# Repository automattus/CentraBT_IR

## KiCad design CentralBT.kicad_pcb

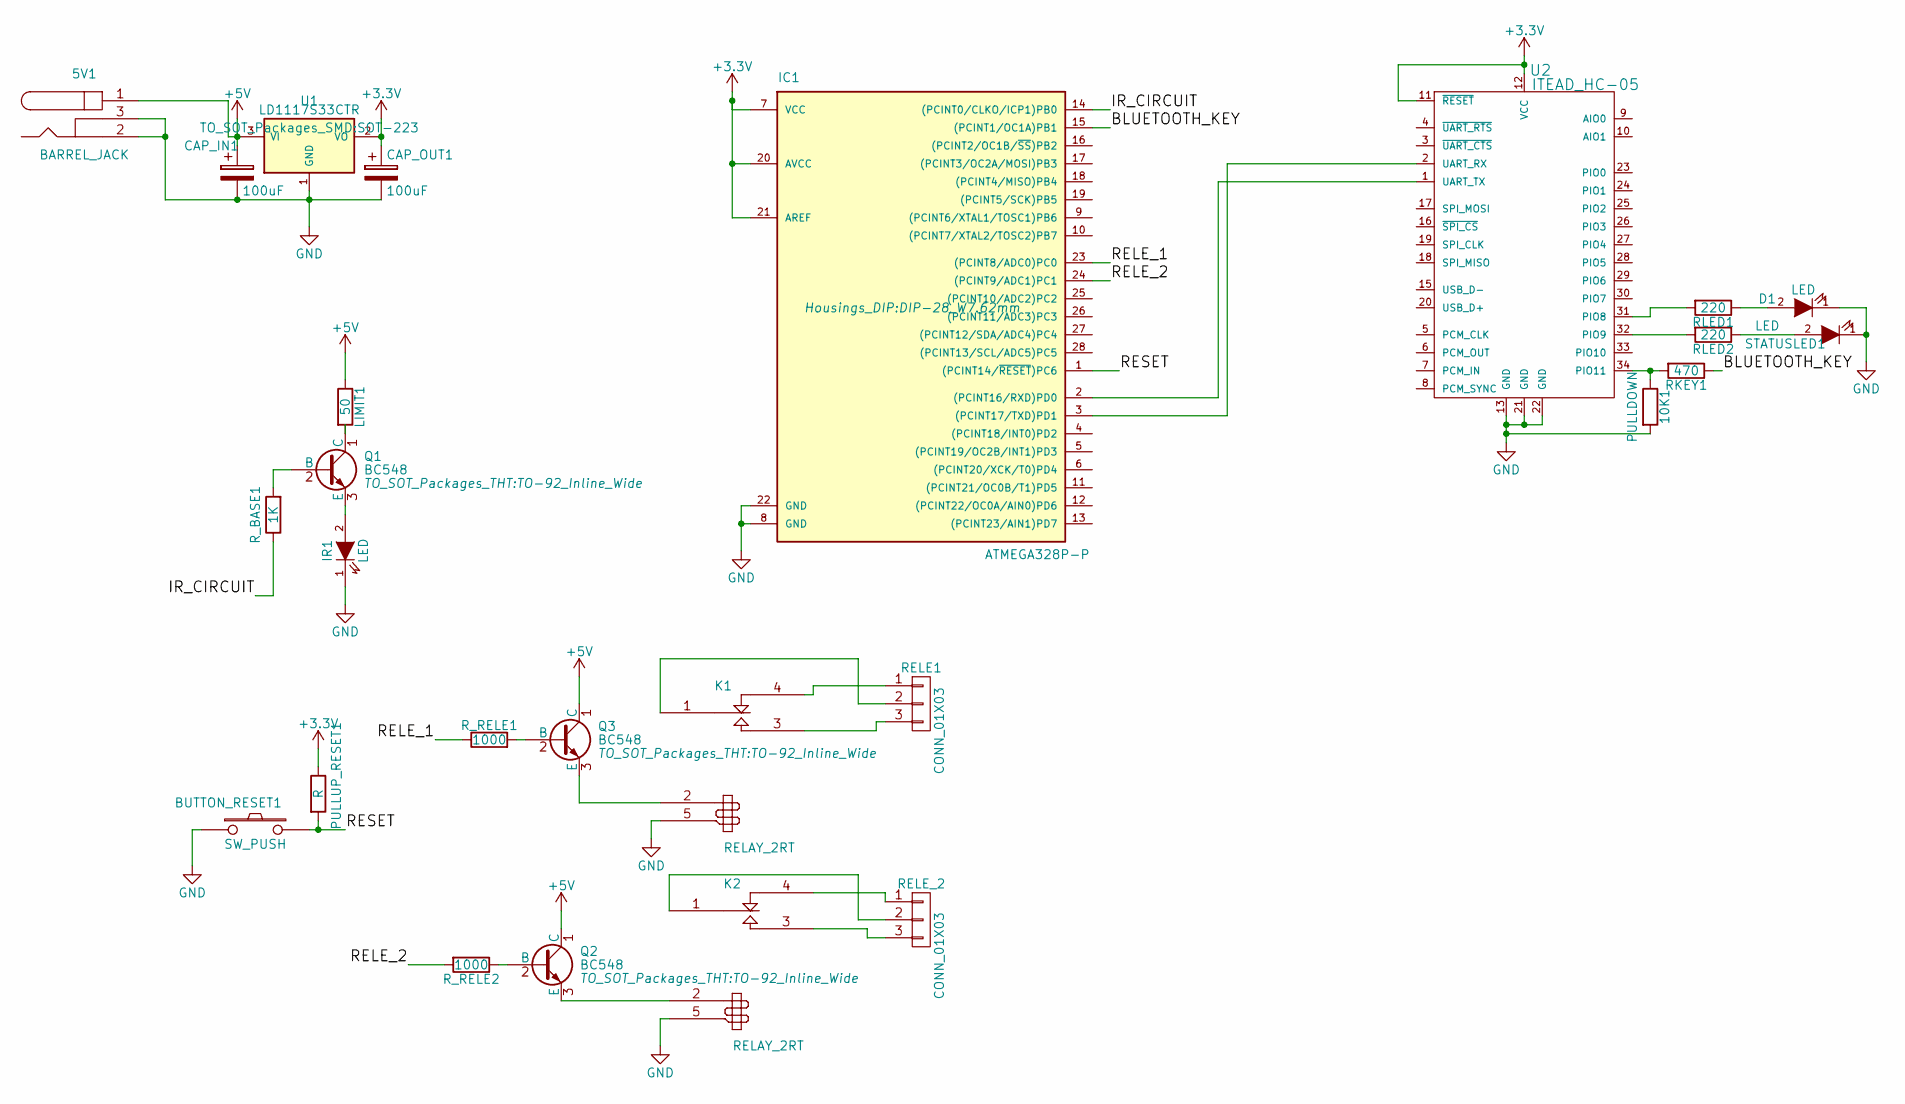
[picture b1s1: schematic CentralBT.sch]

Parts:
5V1: BARREL_JACK
10K1: PULLDOWN; Resistor_Horizontal_RM7mm
BUTTON_RESET1: SW_PUSH; SW_PUSH_SMALL
CAP_IN1: 100uF; C_Radial_D5_L6_P2.5
CAP_OUT1: 100uF; C_Radial_D5_L6_P2.5
D1: LED; LED-3MM
IC1: ATMEGA328P-P; DIP-28_W7.62mm
IR1: LED; LED-5MM
K1, K2: RELAY_2RT; Relay_SANYOU_SRD_Series_Form_C
LIMIT1: 50; Resistor_Horizontal_RM7mm
PULLUP_RESET1: R; Resistor_Horizontal_RM7mm
Q1, Q2, Q3: BC548; TO-92_Inline_Wide
RELE1: CONN_01X03; bornier3
RELE_2: CONN_01X03; bornier3
RKEY1: 470; Resistor_Horizontal_RM7mm
RLED1, RLED2: 220; Resistor_Horizontal_RM7mm
R_BASE1: 1K; Resistor_Horizontal_RM7mm
R_RELE1, R_RELE2: 1000; Resistor_Horizontal_RM7mm
STATUSLED1: LED; LED-3MM
U1: LD1117S33CTR; SOT-223
U2: ITEAD_HC-05

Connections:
+3V3: CAP_OUT1.1, IC1.7 (VCC), IC1.20 (AVCC), IC1.21 (AREF), PULLUP_RESET1.1, U1.2 (VO), U2.11 (~RESET), U2.12 (VCC)
+5V: 5V1.1, CAP_IN1.1, LIMIT1.1, Q2.1 (C), Q3.1 (C), U1.3 (VI)
/BLUETOOTH_KEY: IC1.15 ((PCINT1/OC1A)PB1), RKEY1.1
/IR_CIRCUIT: IC1.14 ((PCINT0/CLKO/ICP1)PB0), R_BASE1.1
/RELE_1: IC1.23 ((PCINT8/ADC0)PC0), R_RELE1.1
/RELE_2: IC1.24 ((PCINT9/ADC1)PC1), R_RELE2.2
/RESET: BUTTON_RESET1.2, IC1.1 ((PCINT14/~RESET~)PC6), PULLUP_RESET1.2
GND: 5V1.2, 5V1.3, 10K1.2, BUTTON_RESET1.1, CAP_IN1.2, CAP_OUT1.2, D1.1 (K), IC1.8 (GND), IC1.22 (GND), IR1.1 (K), K1.5 (GND), K2.5 (GND), STATUSLED1.1 (K), U1.1 (GND), U2.13 (GND), U2.21 (GND), U2.22 (GND)
unnamed: 10K1.1, RKEY1.2, U2.34 (PIO11)
unnamed: D1.2 (A), RLED1.1
unnamed: IC1.2 ((PCINT16/RXD)PD0), U2.1 (UART_TX)
unnamed: IC1.3 ((PCINT17/TXD)PD1), U2.2 (UART_RX)
unnamed: IR1.2 (A), Q1.3 (E)
unnamed: K1.1 (COMUN), RELE1.2
unnamed: K1.2 (CONTROL), Q3.3 (E)
unnamed: K1.3 (NA), RELE1.3
unnamed: K1.4 (NC), RELE1.1
unnamed: K2.1 (COMUN), RELE_2.2
unnamed: K2.2 (CONTROL), Q2.3 (E)
unnamed: K2.3 (NA), RELE_2.3
unnamed: K2.4 (NC), RELE_2.1
unnamed: LIMIT1.2, Q1.1 (C)
unnamed: Q1.2 (B), R_BASE1.2
unnamed: Q2.2 (B), R_RELE2.1
unnamed: Q3.2 (B), R_RELE1.2
unnamed: RLED1.2, U2.31 (PIO8)
unnamed: RLED2.1, STATUSLED1.2 (A)
unnamed: RLED2.2, U2.32 (PIO9)

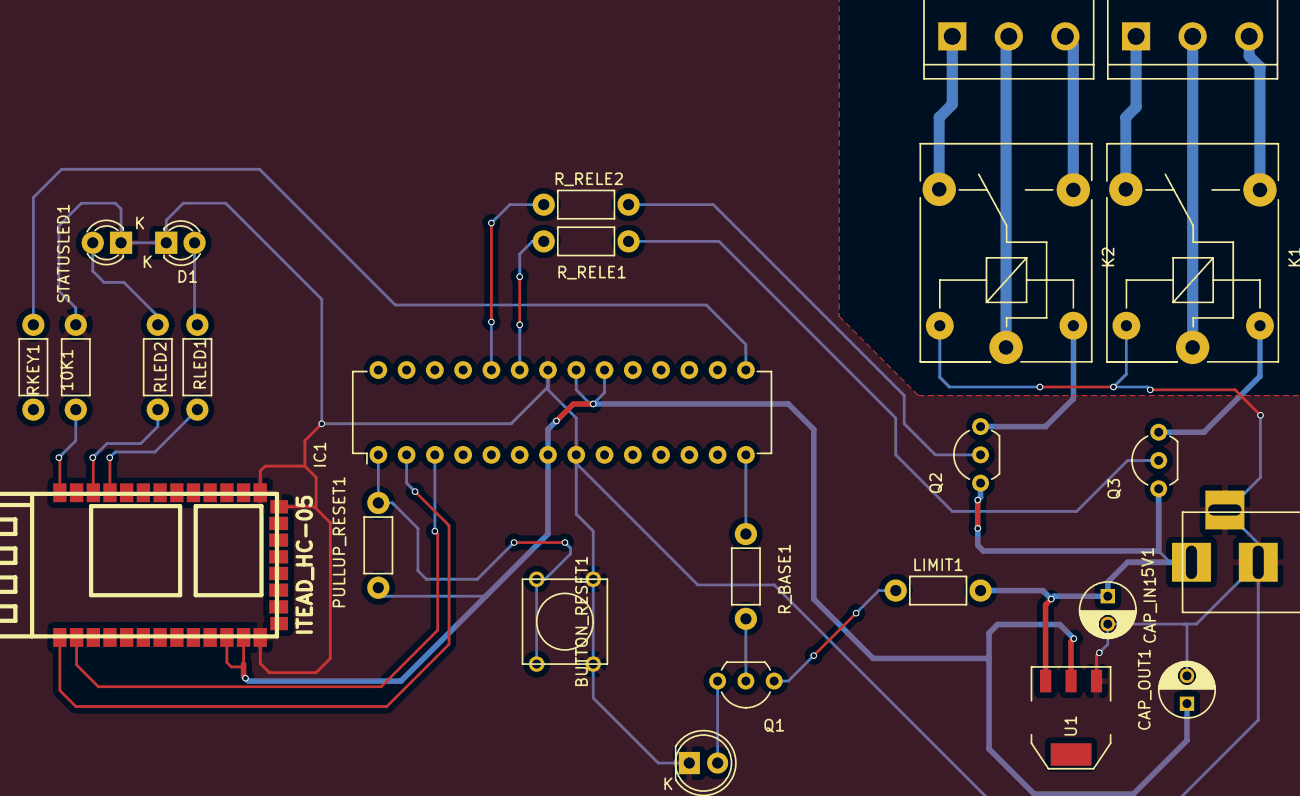
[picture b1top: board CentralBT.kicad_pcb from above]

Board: 2 copper layers, 26 parts (0 on the bottom side), 28 nets.

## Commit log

2016-06-15 :boom::camel: Added .gitattributes & .gitignore files
2016-06-15 1 try
2016-06-15 ajeitei uma besteira que tinha feitp
